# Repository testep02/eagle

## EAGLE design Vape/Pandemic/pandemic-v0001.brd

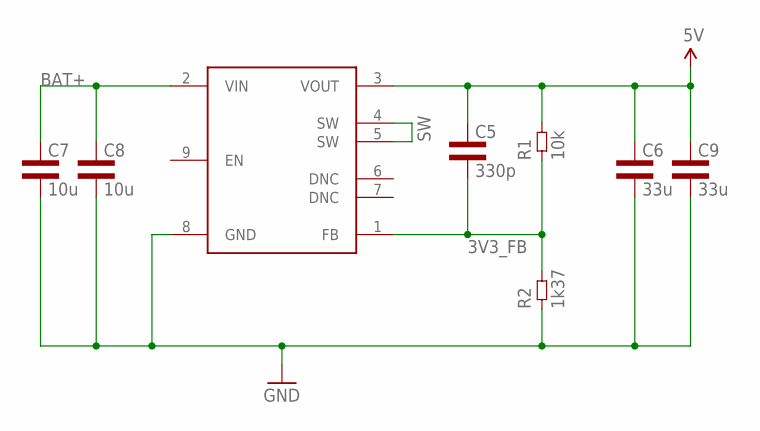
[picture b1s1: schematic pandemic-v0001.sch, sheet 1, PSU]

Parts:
C5: 330p; 0402L3
C6, C9: 33u; 1210L3
C7, C8: 10u; 1210L3
R1: 10k; 0402L3
R2: 1k37; 0402L3
U2: TPSM84209RKH; TPSM84209RKHT

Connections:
3V3_FB: C5.P$2 (2), R1.P$1 (1), R2.P$2 (2), U2.1 (FB)
5V: C5.P$1 (1), C6.P$1 (1), C9.P$1 (1), R1.P$2 (2), U2.3 (VOUT)
BAT+: C7.P$1 (1), C8.P$1 (1), U2.2 (VIN)
GND: C6.P$2 (2), C7.P$2 (2), C8.P$2 (2), C9.P$2 (2), R2.P$1 (1), U2.8 (GND); also elsewhere on the board
SW: U2.4 (SW), U2.5 (SW)

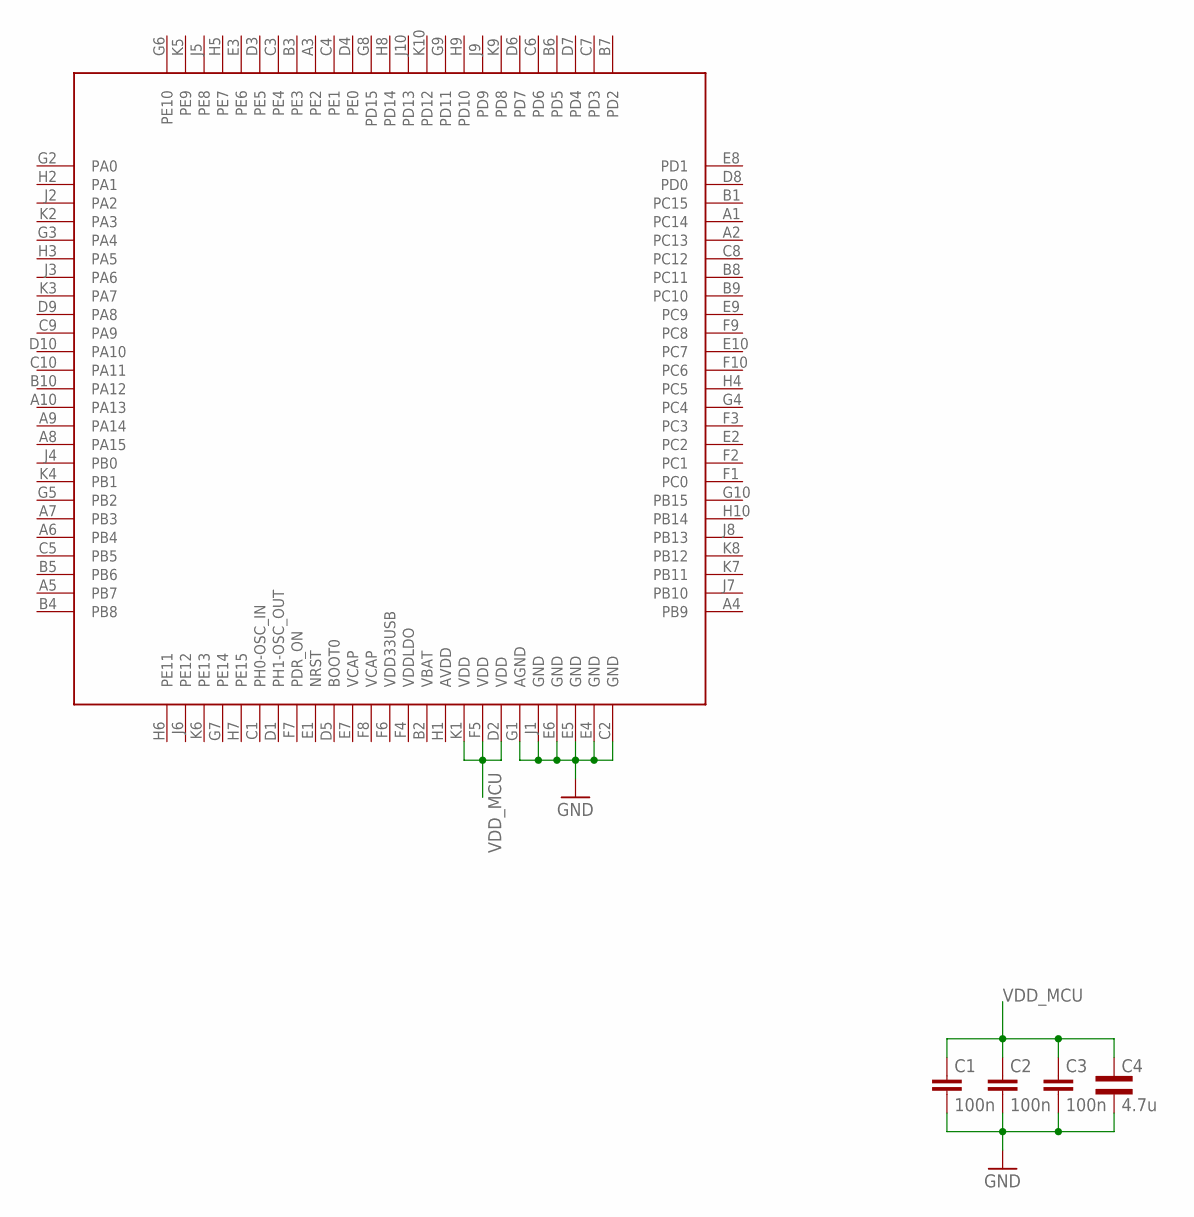
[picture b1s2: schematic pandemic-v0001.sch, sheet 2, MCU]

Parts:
C1, C2, C3: 100n; C0201
C4: 4.7u; 0805L3
U1: STM32H743VIH; BGA100C80P10X10_800X800X110

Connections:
GND: C1.2, C2.2, C3.2, C4.2, U1.C2 (GND), U1.E4 (GND), U1.E5 (GND), U1.E6 (GND), U1.G1 (AGND), U1.J1 (GND); also elsewhere on the board
VDD_MCU: C1.1, C2.1, C3.1, C4.1, U1.D2 (VDD), U1.F5 (VDD), U1.K1 (VDD)

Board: 2 copper layers, 13 parts (3 on the bottom side), 6 nets, no tracks yet.

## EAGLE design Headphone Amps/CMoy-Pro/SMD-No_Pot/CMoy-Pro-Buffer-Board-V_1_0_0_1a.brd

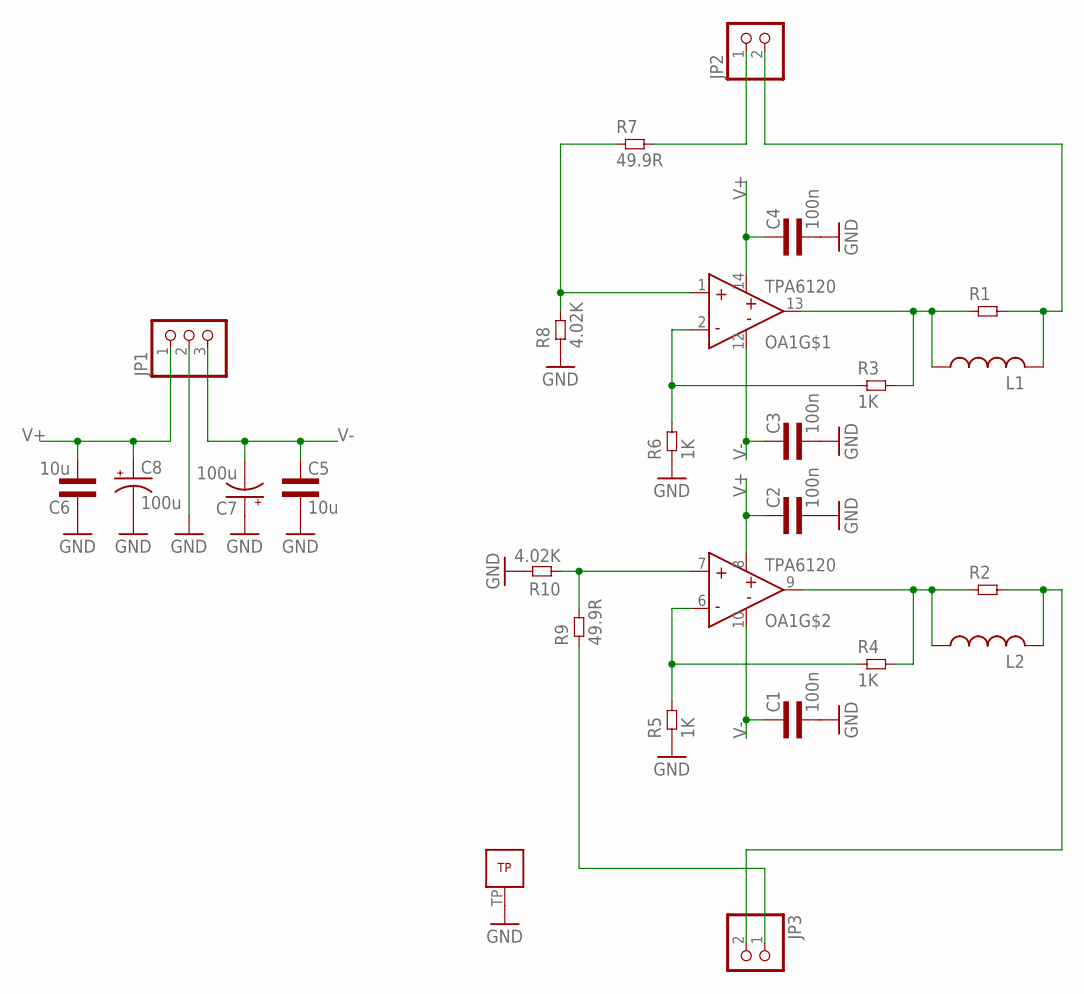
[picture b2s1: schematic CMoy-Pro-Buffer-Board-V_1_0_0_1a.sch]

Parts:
C1, C2, C3, C4: 100n; 0603L3
C5, C6: 10u; 0805L3
C7, C8: 100u; CT7343
JP1: PINHD-1X3; 1X03
JP2, JP3: PINHD-1X2; 1X02
L1, L2: L-USL2012C; L2012C
OA1: TPA6120QFN; S-PVQFN-N14
R1, R2: RES1210L3; 1210L3
R3, R4, R5, R6: 1K; 0603L3
R7, R9: 49.9R; 0603L3
R8, R10: 4.02K; 0603L3

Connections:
GND: C1.P$2 (2), C2.P$2 (2), C3.P$2 (2), C4.P$2 (2), C5.2, C6.1, C7.+, C8.-, JP1.2, OA1.TP, R5.P$1 (1), R6.P$1 (1), R8.P$1 (1), R10.P$2 (2)
unnamed: L2.1, OA1.9 (OUT), R2.P$1 (1), R4.P$2 (2)
unnamed: JP3.2, L2.2, R2.P$2 (2)
unnamed: OA1.6 (IN-), R4.P$1 (1), R5.P$2 (2)
unnamed: L1.1, OA1.13 (OUT), R1.P$1 (1), R3.P$2 (2)
unnamed: JP2.2, L1.2, R1.P$2 (2)
unnamed: OA1.2 (IN-), R3.P$1 (1), R6.P$2 (2)
unnamed: OA1.1 (IN+), R7.P$1 (1), R8.P$2 (2)
unnamed: JP3.1, R9.P$1 (1)
unnamed: OA1.7 (IN+), R9.P$2 (2), R10.P$1 (1)
unnamed: JP2.1, R7.P$2 (2)
V+: C2.P$1 (1), C4.P$1 (1), C6.2, C8.+, JP1.1, OA1.8 (V+), OA1.14 (V+)
V-: C1.P$1 (1), C3.P$1 (1), C5.1, C7.-, JP1.3, OA1.10 (V-), OA1.12 (V-)

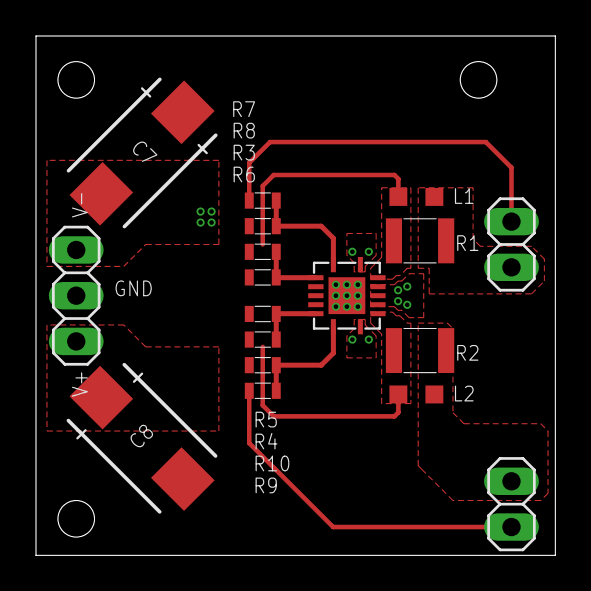
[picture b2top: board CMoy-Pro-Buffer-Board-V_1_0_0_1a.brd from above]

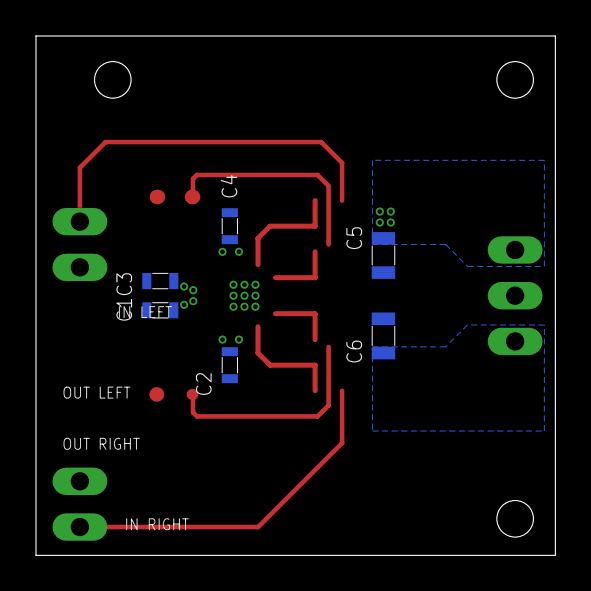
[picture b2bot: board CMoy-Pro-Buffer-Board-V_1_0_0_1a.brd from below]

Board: 4 copper layers, 28.9 x 28.9 mm, 24 parts (6 on the bottom side), 13 nets.

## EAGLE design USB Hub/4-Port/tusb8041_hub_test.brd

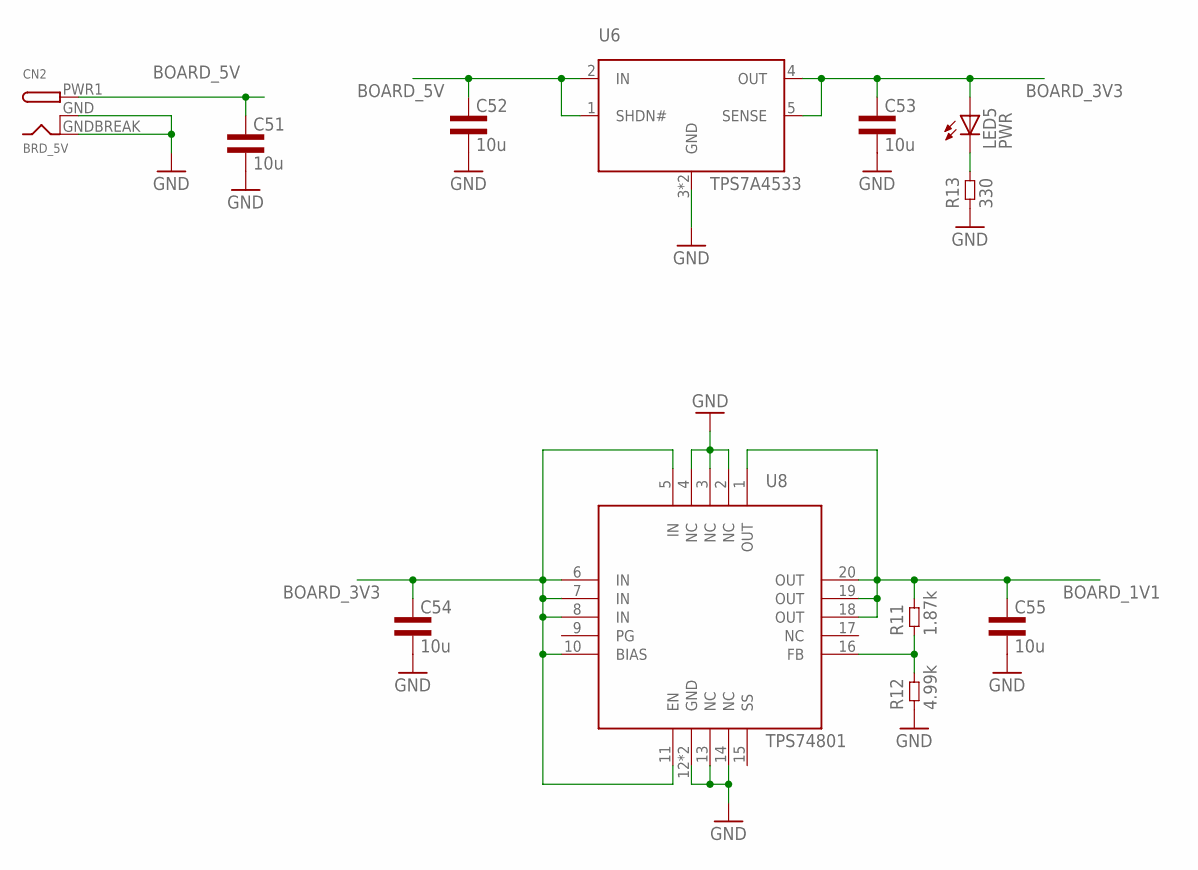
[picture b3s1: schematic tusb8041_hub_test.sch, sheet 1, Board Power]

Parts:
C51, C52, C53, C54, C55: 10u; 1206L3
CN2: BRD_5V; DCJACK_2MM_SMT
LED5: PWR; CHIP-LED0603
R11: 1.87k; 0402L3
R12: 4.99k; 0402L3
R13: 330; 0603L3
U6: BRD_3V3; R-PSFM-G5
U8: BRD_1V1; S-PVQFN-N20

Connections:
BOARD_1V1: C55.1, R11.P$2 (2), U8.1 (OUT), U8.18 (OUT), U8.19 (OUT), U8.20 (OUT); also elsewhere on the board
BOARD_3V3: C53.1, C54.1, LED5.A, U6.4 (OUT), U6.5 (SENSE), U8.5 (IN), U8.6 (IN), U8.7 (IN), U8.8 (IN), U8.10 (BIAS), U8.11 (EN); also elsewhere on the board
BOARD_5V: C51.1, C52.1, CN2.PWR1 (PWR), U6.1 (SHDN#), U6.2 (IN); also elsewhere on the board
GND: C51.2, C52.2, C53.2, C54.2, C55.2, CN2.GND (GNDBREAK), CN2.GNDBREAK (GND), R12.P$1 (1), R13.P$1 (1), U6.3 (GND), U6.TP (GND), U8.2 (NC), U8.3 (NC), U8.4 (NC), U8.12 (GND), U8.13 (NC), U8.14 (NC), U8.TP (GND); also elsewhere on the board
unnamed: LED5.C, R13.P$2 (2)
unnamed: R11.P$1 (1), R12.P$2 (2), U8.16 (FB)

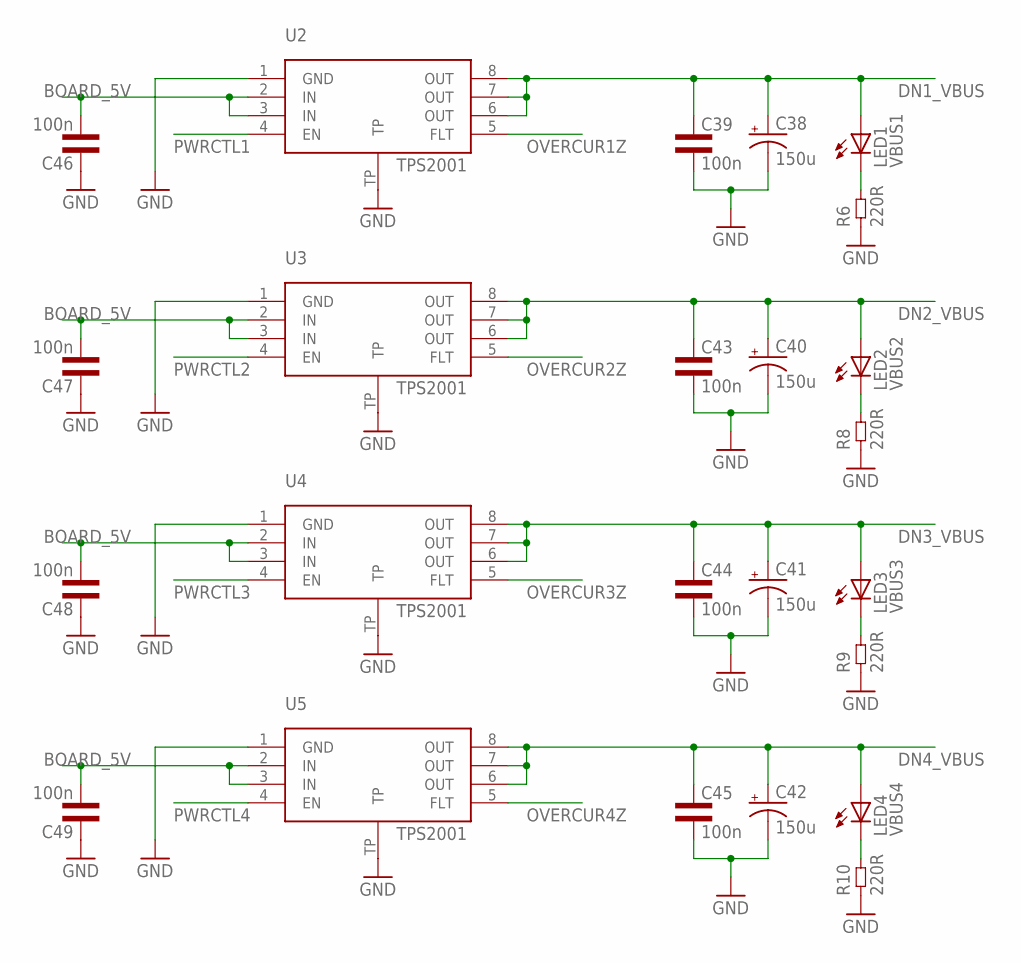
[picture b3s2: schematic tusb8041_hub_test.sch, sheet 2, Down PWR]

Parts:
C38, C40, C41, C42: 150u; CT7343
C39, C43, C44, C45, C46, C47, C48, C49: 100n; 0603L3
LED1: VBUS1; CHIP-LED0603
LED2: VBUS2; CHIP-LED0603
LED3: VBUS3; CHIP-LED0603
LED4: VBUS4; CHIP-LED0603
R6, R8, R9, R10: 220R; 0603L3
U2, U3, U4, U5: USB_5V; S-PDSO-G8

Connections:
BOARD_5V: C46.P$2 (2), C47.P$2 (2), C48.P$2 (2), C49.P$2 (2), U2.2 (IN), U2.3 (IN), U3.2 (IN), U3.3 (IN), U4.2 (IN), U4.3 (IN), U5.2 (IN), U5.3 (IN); also elsewhere on the board
DN1_VBUS: C38.+, C39.P$1 (1), LED1.A, U2.6 (OUT), U2.7 (OUT), U2.8 (OUT); also elsewhere on the board
DN2_VBUS: C40.+, C43.P$1 (1), LED2.A, U3.6 (OUT), U3.7 (OUT), U3.8 (OUT); also elsewhere on the board
DN3_VBUS: C41.+, C44.P$1 (1), LED3.A, U4.6 (OUT), U4.7 (OUT), U4.8 (OUT); also elsewhere on the board
DN4_VBUS: C42.+, C45.P$1 (1), LED4.A, U5.6 (OUT), U5.7 (OUT), U5.8 (OUT); also elsewhere on the board
GND: C38.-, C39.P$2 (2), C40.-, C41.-, C42.-, C43.P$2 (2), C44.P$2 (2), C45.P$2 (2), C46.P$1 (1), C47.P$1 (1), C48.P$1 (1), C49.P$1 (1), R6.P$1 (1), R8.P$1 (1), R9.P$1 (1), R10.P$1 (1), U2.1 (GND), U2.TP, U3.1 (GND), U3.TP, U4.1 (GND), U4.TP, U5.1 (GND), U5.TP; also elsewhere on the board
unnamed: LED1.C, R6.P$2 (2)
unnamed: LED2.C, R8.P$2 (2)
unnamed: LED3.C, R9.P$2 (2)
unnamed: LED4.C, R10.P$2 (2)
OVERCUR1Z: U2.5 (FLT); also elsewhere on the board
OVERCUR2Z: U3.5 (FLT); also elsewhere on the board
OVERCUR3Z: U4.5 (FLT); also elsewhere on the board
OVERCUR4Z: U5.5 (FLT); also elsewhere on the board
PWRCTL1: U2.4 (EN); also elsewhere on the board
PWRCTL2: U3.4 (EN); also elsewhere on the board
PWRCTL3: U4.4 (EN); also elsewhere on the board
PWRCTL4: U5.4 (EN); also elsewhere on the board

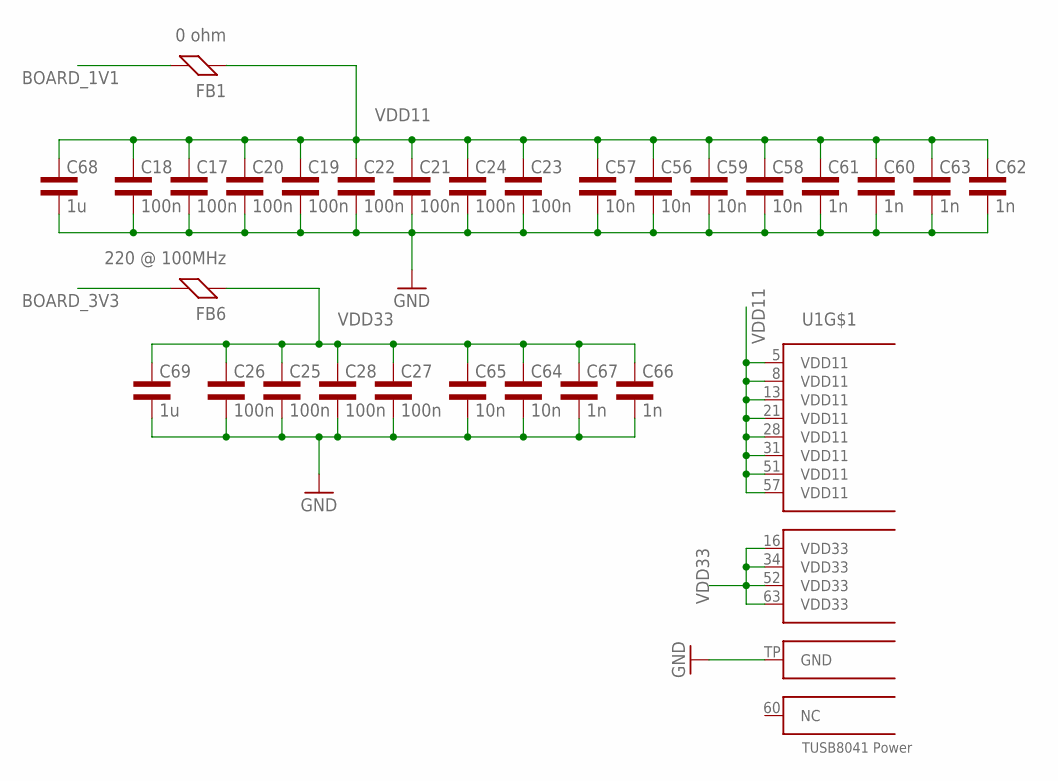
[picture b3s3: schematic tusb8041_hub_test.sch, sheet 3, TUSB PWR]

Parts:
C17, C18, C19, C20, C21, C22, C23, C24, C25, C26, C27, C28: 100n; 0402L3
C56, C57, C58, C59, C64, C65: 10n; 0402L3
C60, C61, C62, C63, C66, C67: 1n; 0402L3
C68, C69: 1u; 0805L3
FB1: 0 ohm; 0603L3
FB6: 220 @ 100MHz; 0603L3
U1: USB_HUB; VQFN64

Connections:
BOARD_1V1: FB1.P$2 (2); also elsewhere on the board
BOARD_3V3: FB6.P$2 (2); also elsewhere on the board
GND: C17.P$2 (2), C18.P$2 (2), C19.P$2 (2), C20.P$2 (2), C21.P$2 (2), C22.P$2 (2), C23.P$2 (2), C24.P$2 (2), C25.P$2 (2), C26.P$2 (2), C27.P$2 (2), C28.P$2 (2), C56.P$2 (2), C57.P$2 (2), C58.P$2 (2), C59.P$2 (2), C60.P$2 (2), C61.P$2 (2), C62.P$2 (2), C63.P$2 (2), C64.P$2 (2), C65.P$2 (2), C66.P$2 (2), C67.P$2 (2), C68.2, C69.2, U1.TP (GND); also elsewhere on the board
VDD11: C17.P$1 (1), C18.P$1 (1), C19.P$1 (1), C20.P$1 (1), C21.P$1 (1), C22.P$1 (1), C23.P$1 (1), C24.P$1 (1), C56.P$1 (1), C57.P$1 (1), C58.P$1 (1), C59.P$1 (1), C60.P$1 (1), C61.P$1 (1), C62.P$1 (1), C63.P$1 (1), C68.1, FB1.P$1 (1), U1.5 (VDD11), U1.8 (VDD11), U1.13 (VDD11), U1.21 (VDD11), U1.28 (VDD11), U1.31 (VDD11), U1.51 (VDD11), U1.57 (VDD11)
VDD33: C25.P$1 (1), C26.P$1 (1), C27.P$1 (1), C28.P$1 (1), C64.P$1 (1), C65.P$1 (1), C66.P$1 (1), C67.P$1 (1), C69.1, FB6.P$1 (1), U1.16 (VDD33), U1.34 (VDD33), U1.52 (VDD33), U1.63 (VDD33); also elsewhere on the board

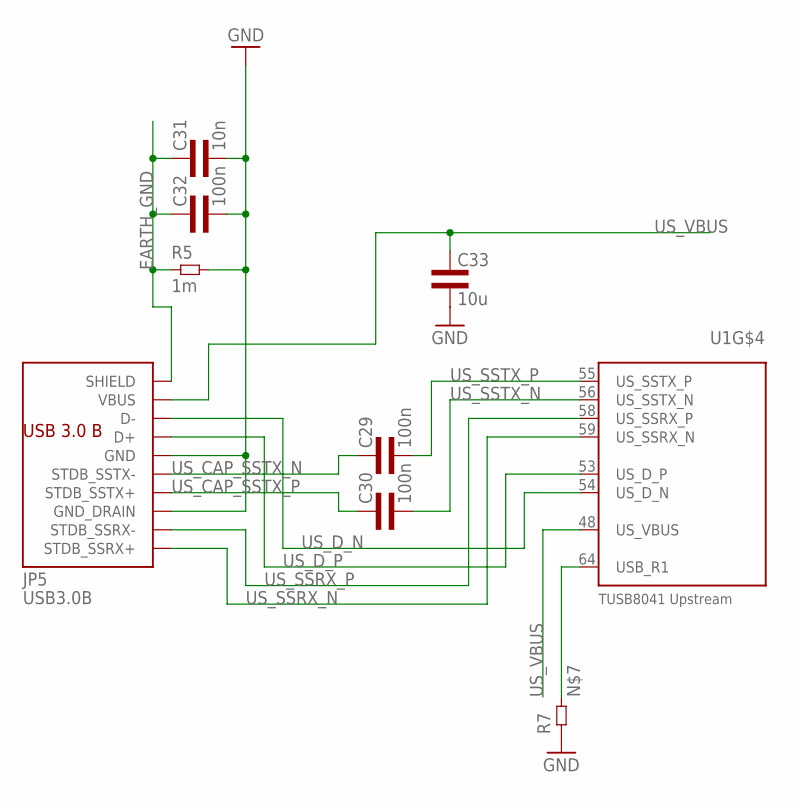
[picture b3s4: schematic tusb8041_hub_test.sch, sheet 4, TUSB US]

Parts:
C29, C30: 100n; 0402L3
C31: 10n; 0603L3
C32: 100n; 0603L3
C33: 10u; 1206L3
JP5: USB3.0B; AMPHENOLUSB3.0B
R5: 1m; 0603L3
R7: RES0402L3; 0402L3
U1: USB_HUB; VQFN64

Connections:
EARTH_GND: C31.P$1 (1), C32.P$1 (1), JP5.10@1 (SHIELD), JP5.10@2 (SHIELD), R5.P$1 (1); also elsewhere on the board
GND: C31.P$2 (2), C32.P$2 (2), C33.2, JP5.4 (GND), JP5.7 (GND_DRAIN), R5.P$2 (2), R7.P$1 (1); also elsewhere on the board
unnamed: R7.P$2 (2), U1.64 (USB_R1)
US_CAP_SSTX_N: C29.P$1 (1), JP5.5 (STDB_SSTX-)
US_CAP_SSTX_P: C30.P$1 (1), JP5.6 (STDB_SSTX+)
US_D_N: JP5.2 (D-), U1.54 (US_D_N)
US_D_P: JP5.3 (D+), U1.53 (US_D_P)
US_SSRX_N: JP5.9 (STDB_SSRX+), U1.59 (US_SSRX_N)
US_SSRX_P: JP5.8 (STDB_SSRX-), U1.58 (US_SSRX_P)
US_SSTX_N: C30.P$2 (2), U1.56 (US_SSTX_N)
US_SSTX_P: C29.P$2 (2), U1.55 (US_SSTX_P)
US_VBUS: C33.1, JP5.1 (VBUS), U1.48 (US_VBUS)

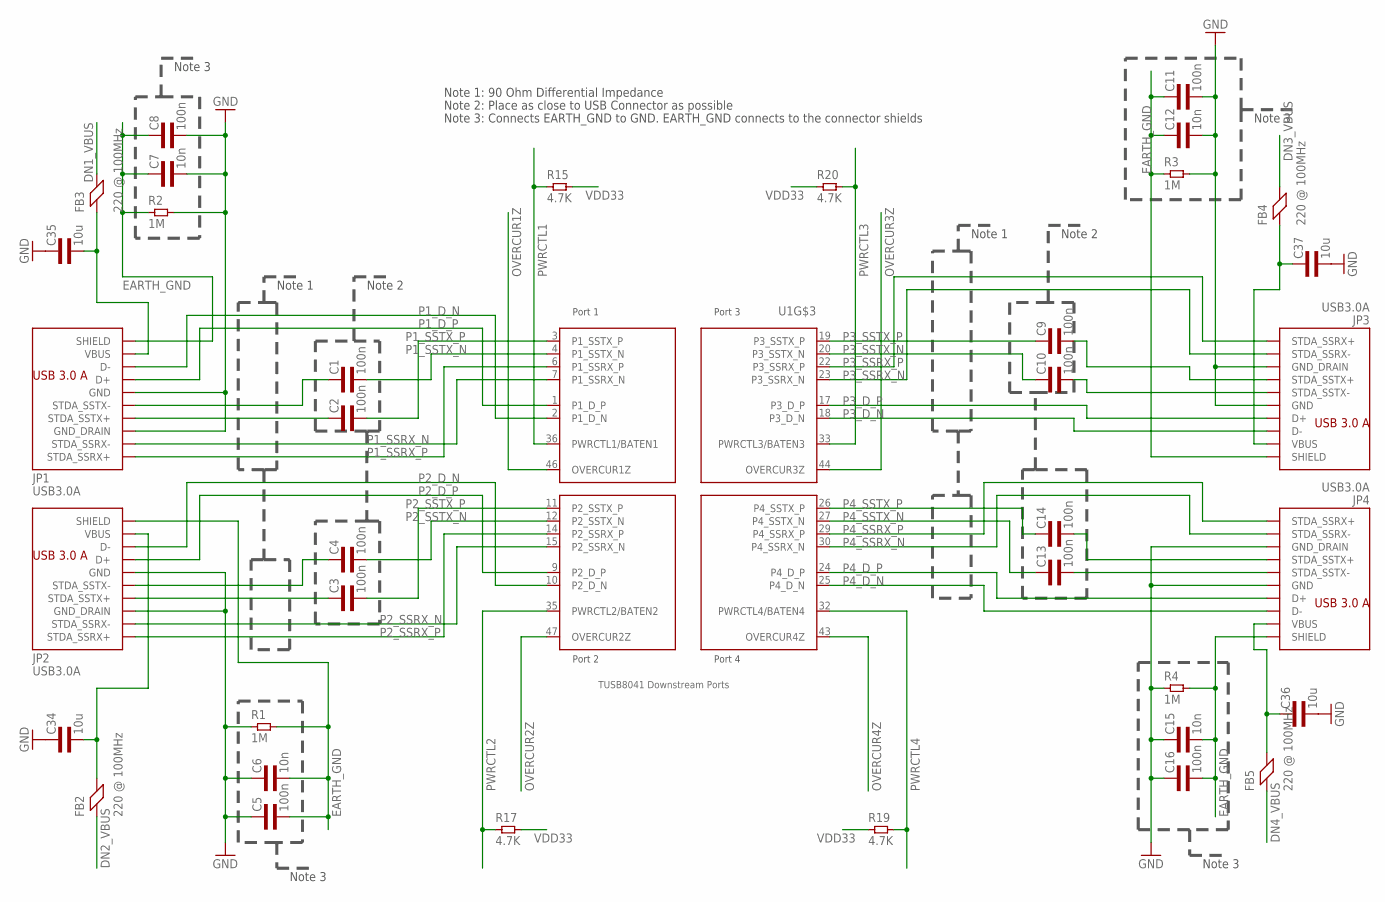
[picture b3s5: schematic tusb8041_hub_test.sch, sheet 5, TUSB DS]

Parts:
C1, C2, C3, C4, C9, C10, C13, C14: 100n; 0402L3
C5, C8, C11, C16: 100n; 0603L3
C6, C7, C12, C15: 10n; 0603L3
C34, C35, C36, C37: 10u; 1206L3
FB2, FB3, FB4, FB5: 220 @ 100MHz; 0603L1
JP1, JP2, JP3, JP4: USB3.0A; AMPHENOLUSB3.0A
R1, R2, R3, R4: 1M; 0603L3
R15, R17, R19, R20: 4.7K; 0402L3
U1: USB_HUB; VQFN64

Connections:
DN1_VBUS: FB3.2; also elsewhere on the board
DN2_VBUS: FB2.1; also elsewhere on the board
DN3_VBUS: FB4.2; also elsewhere on the board
DN4_VBUS: FB5.1; also elsewhere on the board
EARTH_GND: C5.P$2 (2), C6.P$2 (2), C7.P$1 (1), C8.P$1 (1), C11.P$1 (1), C12.P$1 (1), C15.P$2 (2), C16.P$2 (2), JP1.10@1 (SHIELD), JP1.10@2 (SHIELD), JP2.10@1 (SHIELD), JP2.10@2 (SHIELD), JP3.10@1 (SHIELD), JP3.10@2 (SHIELD), JP4.10@1 (SHIELD), JP4.10@2 (SHIELD), R1.P$2 (2), R2.P$1 (1), R3.P$1 (1), R4.P$2 (2); also elsewhere on the board
GND: C5.P$1 (1), C6.P$1 (1), C7.P$2 (2), C8.P$2 (2), C11.P$2 (2), C12.P$2 (2), C15.P$1 (1), C16.P$1 (1), C34.1, C35.1, C36.2, C37.2, JP1.4 (GND), JP1.7 (GND_DRAIN), JP2.4 (GND), JP2.7 (GND_DRAIN), JP3.4 (GND), JP3.7 (GND_DRAIN), JP4.4 (GND), JP4.7 (GND_DRAIN), R1.P$1 (1), R2.P$2 (2), R3.P$2 (2), R4.P$1 (1); also elsewhere on the board
unnamed: C35.2, FB3.1, JP1.1 (VBUS)
unnamed: C34.2, FB2.2, JP2.1 (VBUS)
unnamed: C37.1, FB4.1, JP3.1 (VBUS)
unnamed: C36.1, FB5.2, JP4.1 (VBUS)
OVERCUR1Z: U1.46 (OVERCUR1Z); also elsewhere on the board
OVERCUR2Z: U1.47 (OVERCUR2Z); also elsewhere on the board
OVERCUR3Z: U1.44 (OVERCUR3Z); also elsewhere on the board
OVERCUR4Z: U1.43 (OVERCUR4Z); also elsewhere on the board
P1_CAP_SSTX_N: C1.P$1 (1), JP1.8 (STDA_SSTX-)
P1_CAP_SSTX_P: C2.P$1 (1), JP1.9 (STDA_SSTX+)
P1_D_N: JP1.2 (D-), U1.2 (P1_D_N)
P1_D_P: JP1.3 (D+), U1.1 (P1_D_P)
P1_SSRX_N: JP1.5 (STDA_SSRX-), U1.7 (P1_SSRX_N)
P1_SSRX_P: JP1.6 (STDA_SSRX+), U1.6 (P1_SSRX_P)
P1_SSTX_N: C1.P$2 (2), U1.4 (P1_SSTX_N)
P1_SSTX_P: C2.P$2 (2), U1.3 (P1_SSTX_P)
P2_CAP_SSTX_N: C4.P$1 (1), JP2.8 (STDA_SSTX-)
P2_CAP_SSTX_P: C3.P$1 (1), JP2.9 (STDA_SSTX+)
P2_D_N: JP2.2 (D-), U1.10 (P2_D_N)
P2_D_P: JP2.3 (D+), U1.9 (P2_D_P)
P2_SSRX_N: JP2.5 (STDA_SSRX-), U1.15 (P2_SSRX_N)
P2_SSRX_P: JP2.6 (STDA_SSRX+), U1.14 (P2_SSRX_P)
P2_SSTX_N: C4.P$2 (2), U1.12 (P2_SSTX_N)
P2_SSTX_P: C3.P$2 (2), U1.11 (P2_SSTX_P)
P3_CAP_SSTX_N: C10.P$2 (2), JP3.8 (STDA_SSTX-)
P3_CAP_SSTX_P: C9.P$2 (2), JP3.9 (STDA_SSTX+)
P3_D_N: JP3.2 (D-), U1.18 (P3_D_N)
P3_D_P: JP3.3 (D+), U1.17 (P3_D_P)
P3_SSRX_N: JP3.5 (STDA_SSRX-), U1.23 (P3_SSRX_N)
P3_SSRX_P: JP3.6 (STDA_SSRX+), U1.22 (P3_SSRX_P)
P3_SSTX_N: C10.P$1 (1), U1.20 (P3_SSTX_N)
P3_SSTX_P: C9.P$1 (1), U1.19 (P3_SSTX_P)
P4_CAP_SSTX_N: C13.P$2 (2), JP4.8 (STDA_SSTX-)
P4_CAP_SSTX_P: C14.P$2 (2), JP4.9 (STDA_SSTX+)
P4_D_N: JP4.2 (D-), U1.25 (P4_D_N)
P4_D_P: JP4.3 (D+), U1.24 (P4_D_P)
P4_SSRX_N: JP4.5 (STDA_SSRX-), U1.30 (P4_SSRX_N)
P4_SSRX_P: JP4.6 (STDA_SSRX+), U1.29 (P4_SSRX_P)
P4_SSTX_N: C13.P$1 (1), U1.27 (P4_SSTX_N)
P4_SSTX_P: C14.P$1 (1), U1.26 (P4_SSTX_P)
PWRCTL1: R15.P$1 (1), U1.36 (PWRCTL1/BATEN1); also elsewhere on the board
PWRCTL2: R17.P$1 (1), U1.35 (PWRCTL2/BATEN2); also elsewhere on the board
PWRCTL3: R20.P$2 (2), U1.33 (PWRCTL3/BATEN3); also elsewhere on the board
PWRCTL4: R19.P$2 (2), U1.32 (PWRCTL4/BATEN4); also elsewhere on the board
VDD33: R15.P$2 (2), R17.P$2 (2), R19.P$1 (1), R20.P$1 (1); also elsewhere on the board

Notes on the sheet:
Note 1
Note 2
Note 3
Note 1: 90 Ohm Differential Impedance
Note 2: Place as close to USB Connector as possible
Note 3: Connects EARTH_GND to GND. EARTH_GND connects to the connector shields

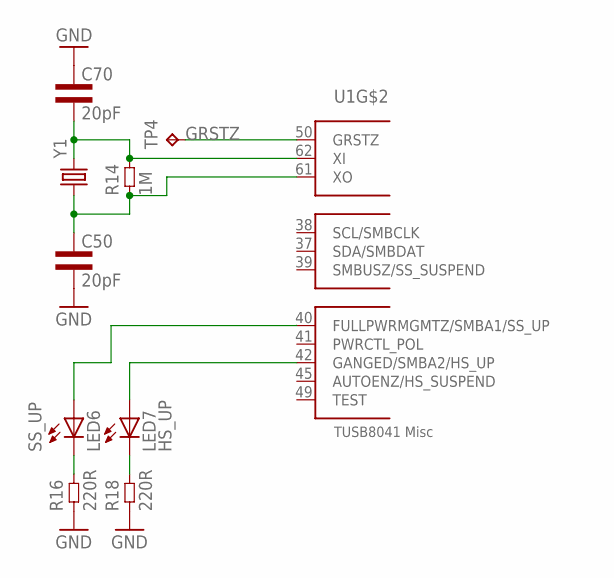
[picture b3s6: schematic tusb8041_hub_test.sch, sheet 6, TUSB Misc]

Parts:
C50, C70: 20pF; 0402L3
LED6: SS_UP; CHIPLED_0603
LED7: HS_UP; CHIPLED_0603
R14: 1M; 0402L3
R16, R18: 220R; 0402L3
TP4: TPTP10R; TP10R
U1: USB_HUB; VQFN64
Y1: CRYSTALHC49US; HC49US

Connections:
CLK_N: C70.P$2 (2), R14.P$2 (2), U1.62 (XI), Y1.2
CLK_P: C50.P$1 (1), R14.P$1 (1), U1.61 (XO), Y1.1
GND: C50.P$2 (2), C70.P$1 (1), R16.P$1 (1), R18.P$1 (1); also elsewhere on the board
GRSTZ: TP4.TP, U1.50 (GRSTZ)
unnamed: LED6.C, R16.P$2 (2)
unnamed: LED7.C, R18.P$2 (2)
unnamed: LED7.A, U1.42 (GANGED/SMBA2/HS_UP)
unnamed: LED6.A, U1.40 (FULLPWRMGMTZ/SMBA1/SS_UP)

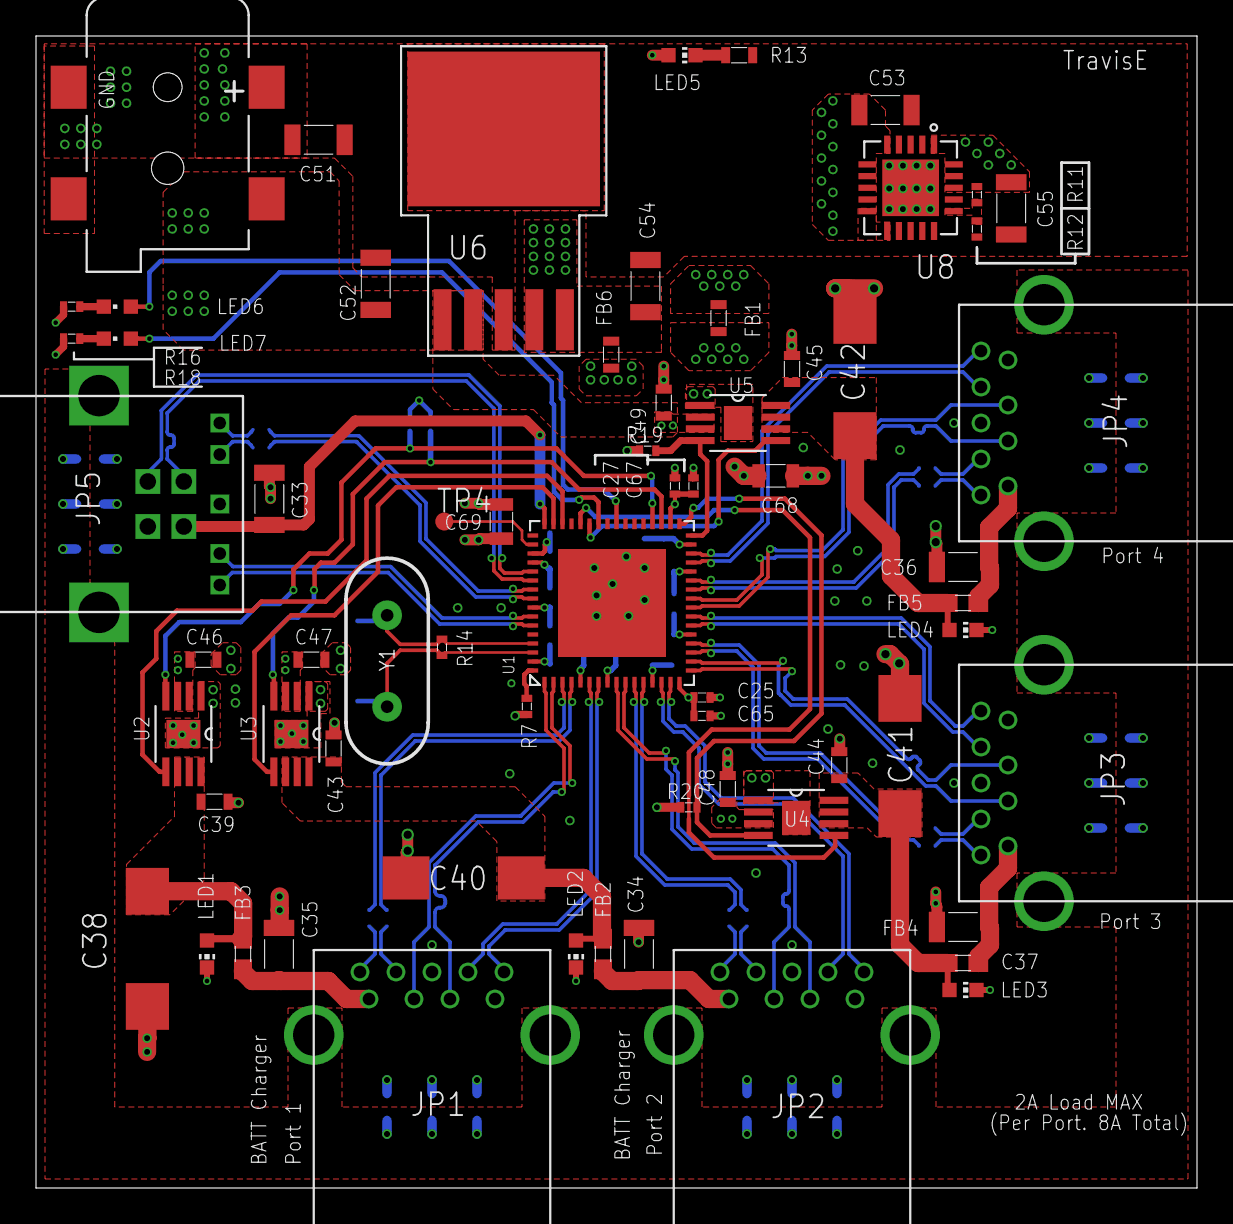
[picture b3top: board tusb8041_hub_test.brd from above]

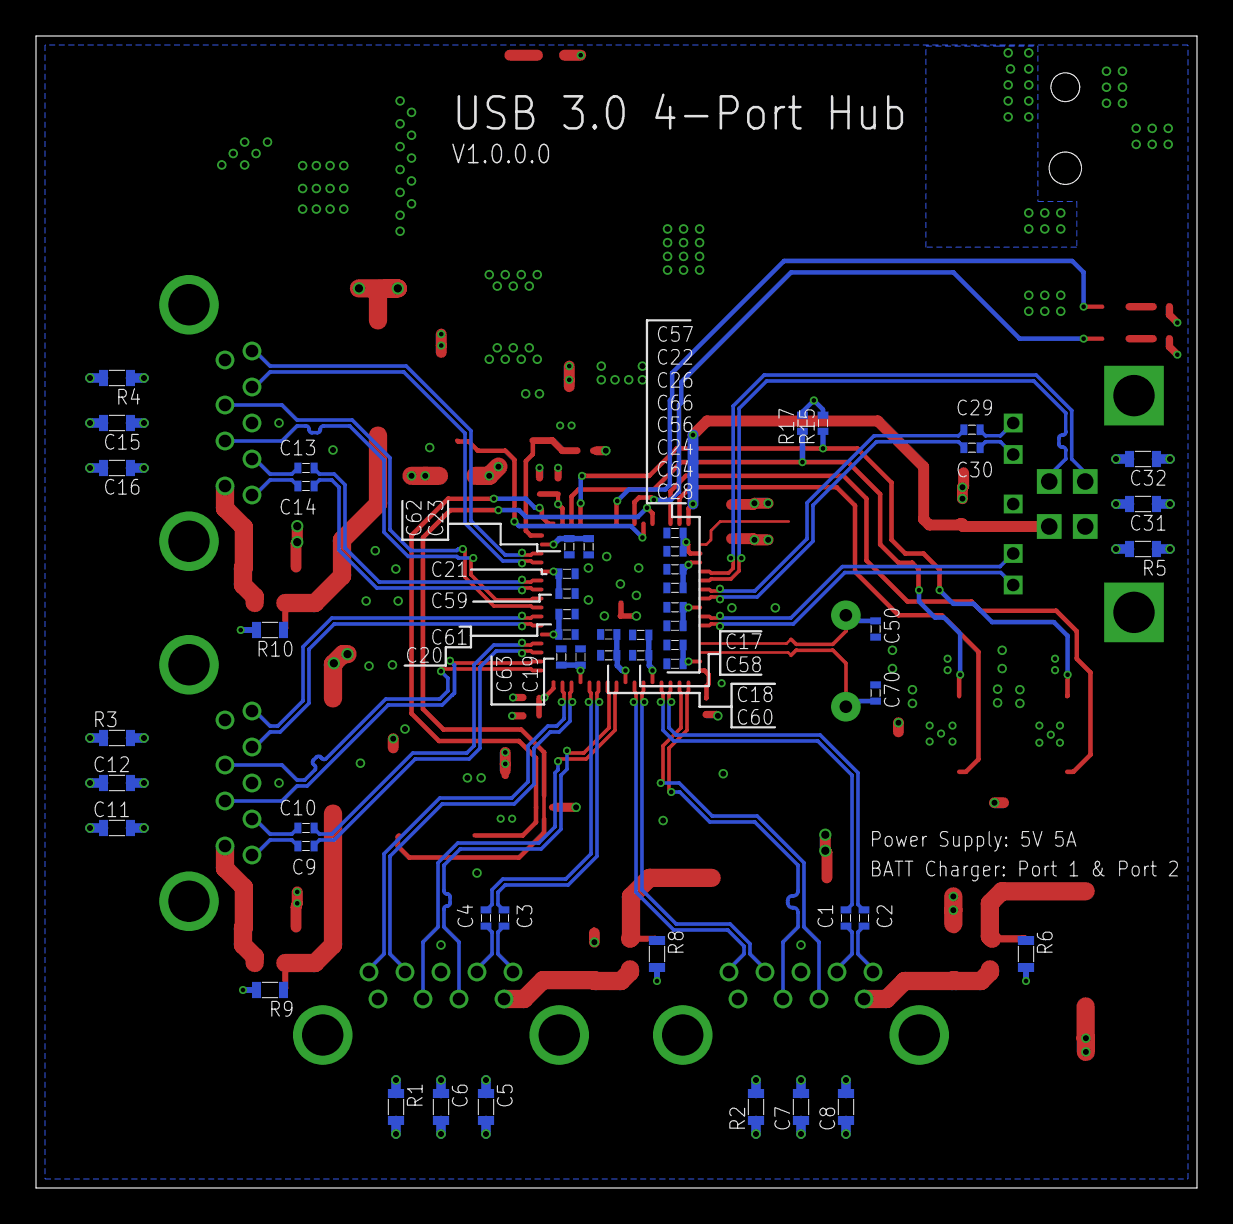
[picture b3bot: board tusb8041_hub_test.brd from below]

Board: 4 copper layers, 64.5 x 64.0 mm, 118 parts (53 on the bottom side), 78 nets.

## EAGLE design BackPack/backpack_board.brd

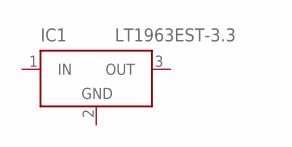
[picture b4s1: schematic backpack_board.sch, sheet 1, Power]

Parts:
IC1: LT1963EST-3.3; SOT223

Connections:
GND: IC1.2 (GND), IC1.4 (GND)

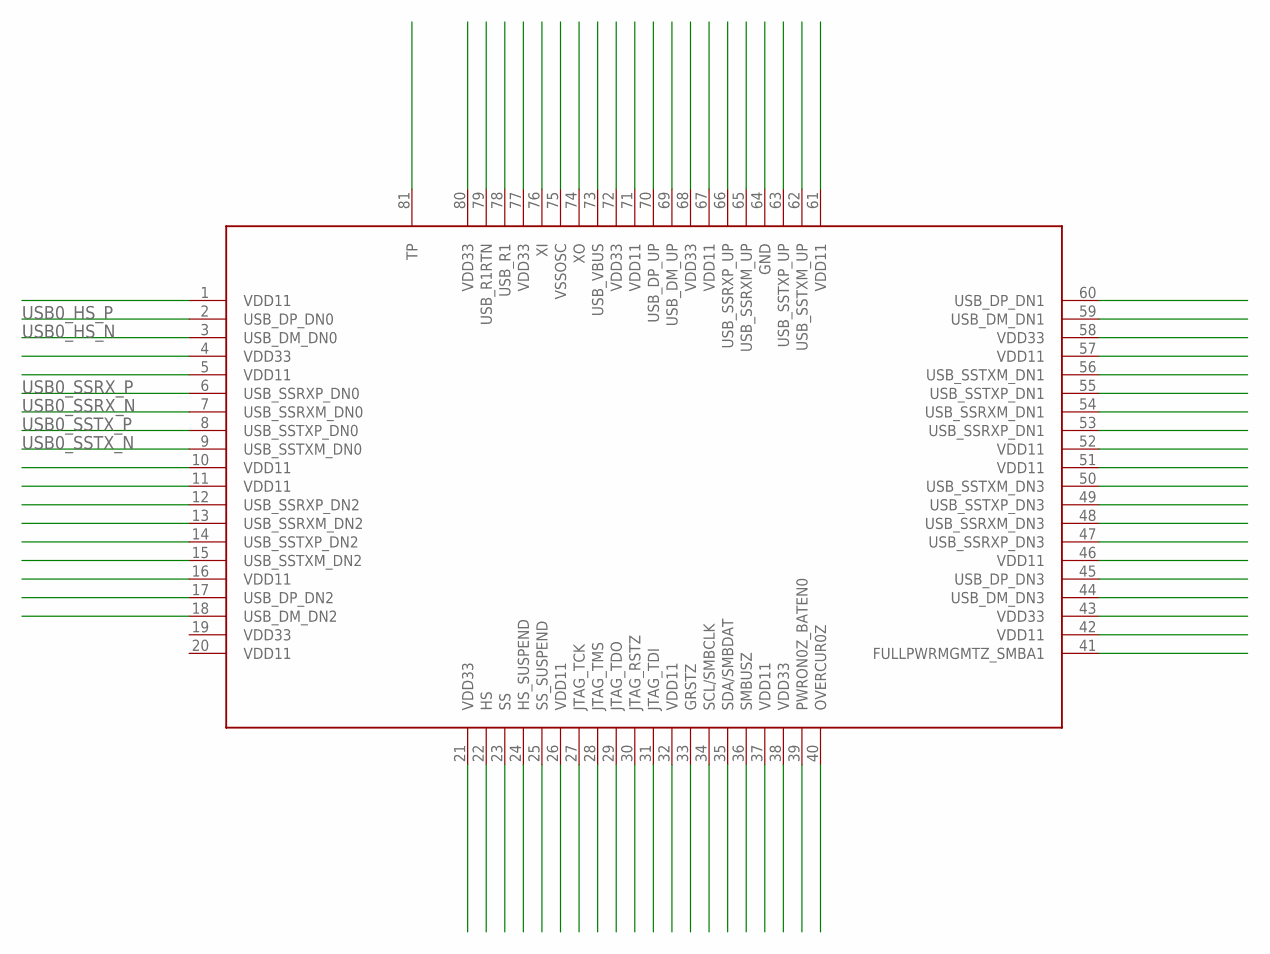
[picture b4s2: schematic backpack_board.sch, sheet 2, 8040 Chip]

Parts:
U$2: TUSB8040PFP; S-PQFP-G80

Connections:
USB0_HS_N: U$2.3 (USB_DM_DN0); also elsewhere on the board
USB0_HS_P: U$2.2 (USB_DP_DN0); also elsewhere on the board
USB0_SSRX_N: U$2.7 (USB_SSRXM_DN0); also elsewhere on the board
USB0_SSRX_P: U$2.6 (USB_SSRXP_DN0); also elsewhere on the board
USB0_SSTX_N: U$2.9 (USB_SSTXM_DN0); also elsewhere on the board
USB0_SSTX_P: U$2.8 (USB_SSTXP_DN0); also elsewhere on the board

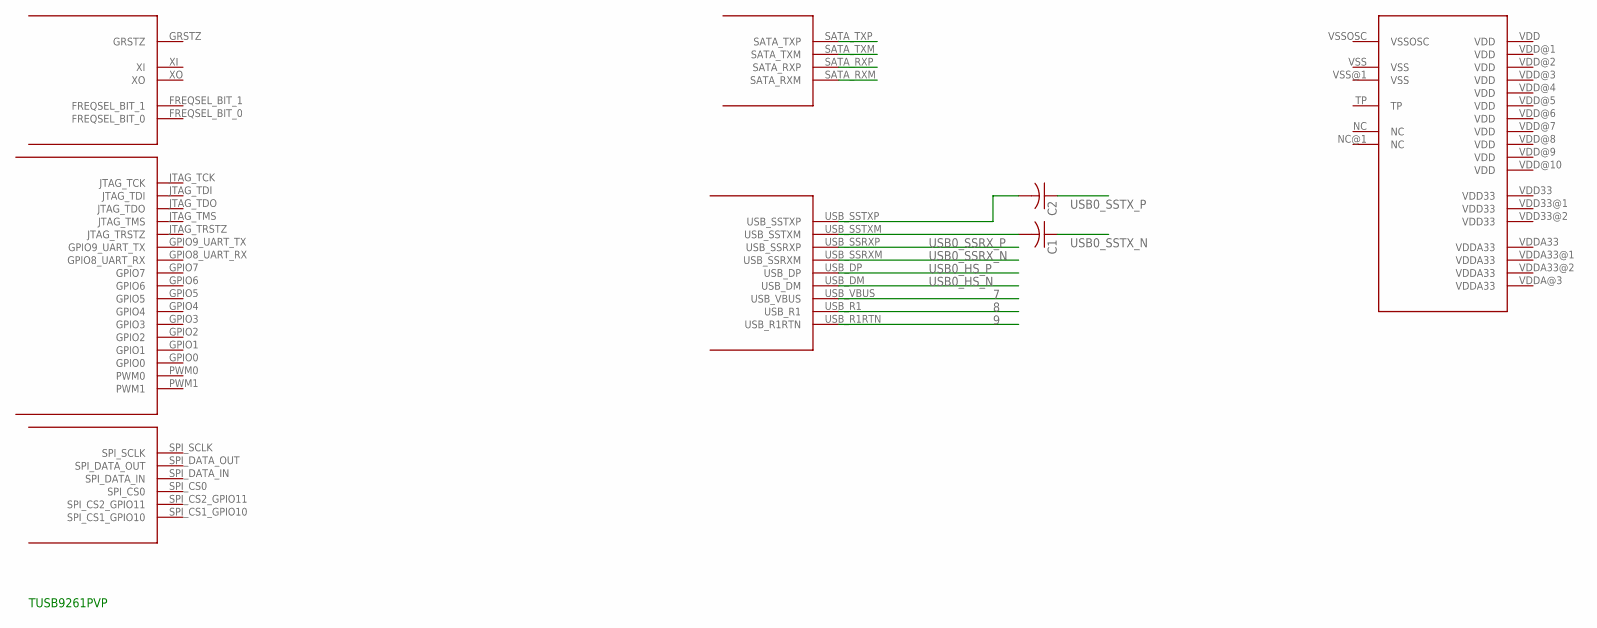
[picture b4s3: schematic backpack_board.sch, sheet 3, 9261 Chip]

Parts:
C1, C2: C-USC0402; C0402
U$1: TUSB9261PVP; S-PQFP-G64

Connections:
7: U$1.USB_VBUS
8: U$1.USB_R1
9: U$1.USB_R1RTN
NC: U$1.NC, U$1.NC@1 (NC)
SATA_SSTXP_N: C1.2, U$1.USB_SSTXM
SATA_SSTXP_P: C2.2, U$1.USB_SSTXP
TP: U$1.TP
USB0_HS_N: U$1.USB_DM; also elsewhere on the board
USB0_HS_P: U$1.USB_DP; also elsewhere on the board
USB0_SSRX_N: U$1.USB_SSRXM; also elsewhere on the board
USB0_SSRX_P: U$1.USB_SSRXP; also elsewhere on the board
USB0_SSTX_N: C1.1; also elsewhere on the board
USB0_SSTX_P: C2.1; also elsewhere on the board
VDD: U$1.VDD, U$1.VDD@1 (VDD), U$1.VDD@2 (VDD), U$1.VDD@3 (VDD), U$1.VDD@4 (VDD), U$1.VDD@5 (VDD), U$1.VDD@6 (VDD), U$1.VDD@7 (VDD), U$1.VDD@8 (VDD), U$1.VDD@9 (VDD), U$1.VDD@10 (VDD)
VDD33: U$1.VDD33, U$1.VDD33@1 (VDD33), U$1.VDD33@2 (VDD33)
VDDA33: U$1.VDDA33, U$1.VDDA33@1 (VDDA33), U$1.VDDA33@2 (VDDA33), U$1.VDDA@3 (VDDA33)
VSS: U$1.VSS, U$1.VSS@1 (VSS)
VSSOSC: U$1.VSSOSC

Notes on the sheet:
TUSB9261PVP

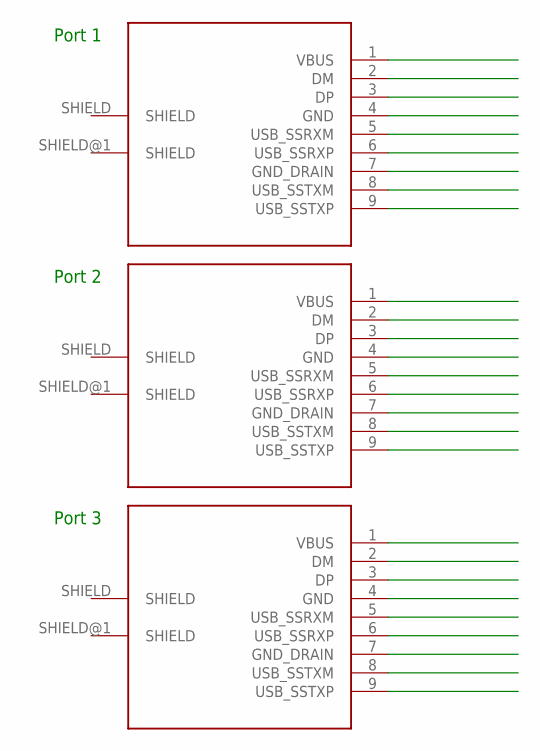
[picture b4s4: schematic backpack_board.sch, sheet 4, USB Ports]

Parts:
U$3, U$4, U$5: USB_SS_CONN_TYPE_A; R_A_DIP

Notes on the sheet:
Port 1
Port 2
Port 3

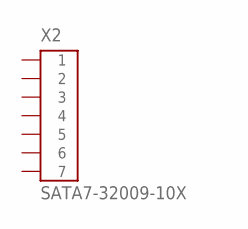
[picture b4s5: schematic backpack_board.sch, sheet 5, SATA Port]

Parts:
X2: SATA7-32009-10X; CCATA_32009_10X

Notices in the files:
parts and their libraries:
SparkFun-Aesthetics: Licensing: CC v3.0 Share-Alike You are welcome to use this library for commercial purposes.
